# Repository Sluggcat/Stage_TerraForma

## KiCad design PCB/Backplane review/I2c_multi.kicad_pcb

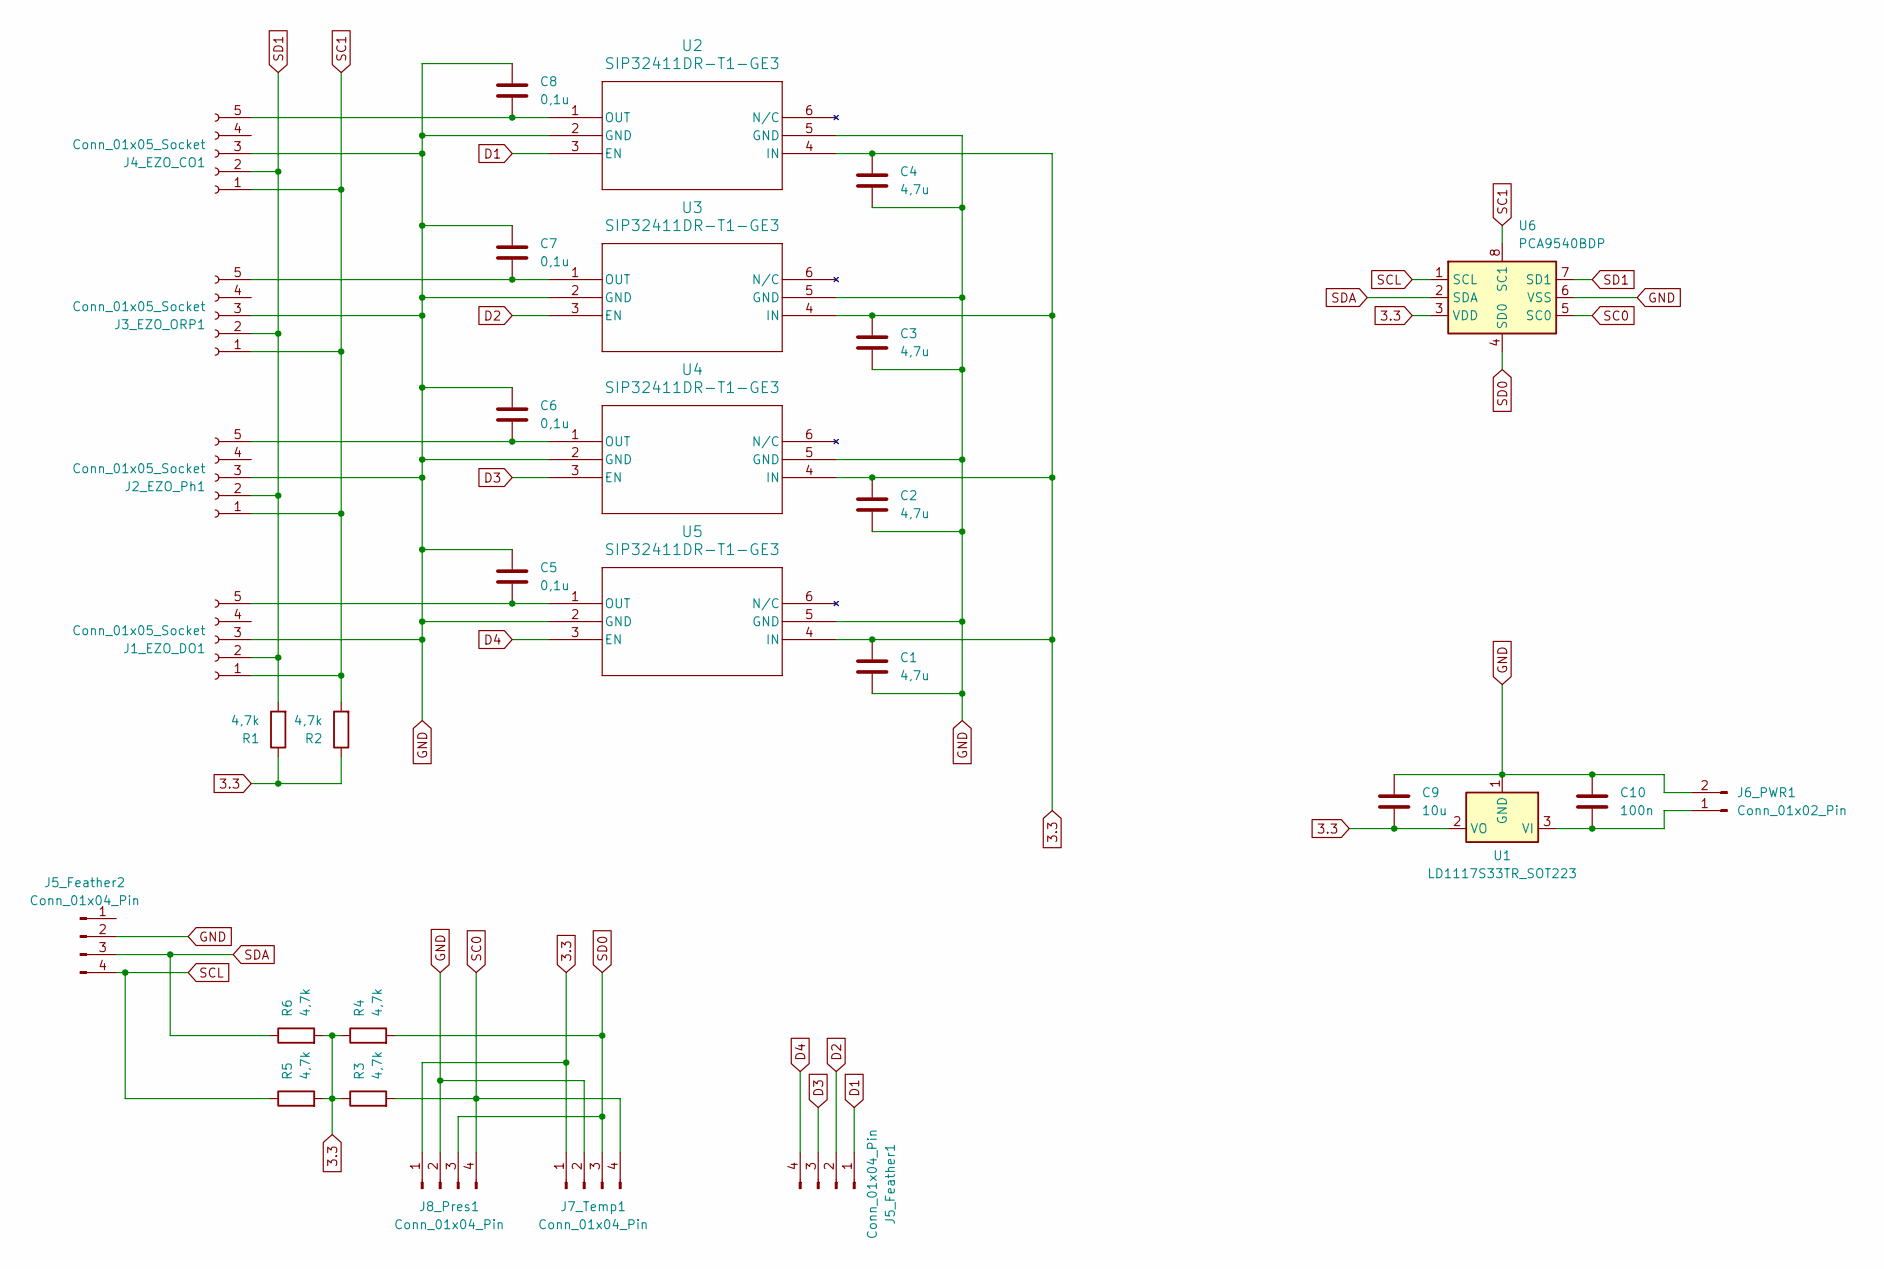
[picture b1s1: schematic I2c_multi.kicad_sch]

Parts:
C1, C2, C3, C4: 4,7u; C_0603_1608Metric_Pad1.08x0.95mm_HandSolder
C5, C6, C7, C8: 0,1u; C_0603_1608Metric_Pad1.08x0.95mm_HandSolder
C9: 10u; C_0603_1608Metric_Pad1.08x0.95mm_HandSolder
C10: 100n; C_0603_1608Metric_Pad1.08x0.95mm_HandSolder
J1_EZO_DO1, J2_EZO_Ph1, J3_EZO_ORP1, J4_EZO_CO1: Conn_01x05_Socket; PinSocket_1x05_P2.54mm_Vertical
J5_Feather1, J5_Feather2, J7_Temp1, J8_Pres1: Conn_01x04_Pin; PinSocket_1x04_P2.54mm_Vertical
J6_PWR1: Conn_01x02_Pin; PinSocket_1x02_P2.54mm_Vertical
R1, R2, R3, R4, R5, R6: 4,7k; R_0603_1608Metric_Pad0.98x0.95mm_HandSolder
U1: LD1117S33TR_SOT223; SOT-223-3_TabPin2
U2, U3, U4, U5: SIP32411DR-T1-GE3; SC_DR-T1-GE3_VIS
U6: PCA9540BDP; TSSOP-8_4.4x3mm_P0.65mm

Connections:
3.3: C1.2, C2.1, C3.1, C4.1, C9.2, J7_Temp1.1, J8_Pres1.1, R1.1, R2.1, R3.1, R4.1, R5.2, R6.2, U1.2 (VO), U2.4 (IN), U3.4 (IN), U4.4 (IN), U5.4 (IN), U6.3 (VDD)
D1: J5_Feather1.1, U2.3 (EN)
D2: J5_Feather1.2, U3.3 (EN)
D3: J5_Feather1.3, U4.3 (EN)
D4: J5_Feather1.4, U5.3 (EN)
GND: C1.1, C2.2, C3.2, C4.2, C5.1, C6.1, C7.1, C8.2, C9.1, C10.1, J1_EZO_DO1.3, J2_EZO_Ph1.3, J3_EZO_ORP1.3, J4_EZO_CO1.3, J5_Feather2.2, J6_PWR1.2, J7_Temp1.2, J8_Pres1.2, U1.1 (GND), U2.2 (GND), U2.5 (GND), U3.2 (GND), U3.5 (GND), U4.2 (GND), U4.5 (GND), U5.2 (GND), U5.5 (GND), U6.6 (VSS)
unnamed: C5.2, J1_EZO_DO1.5, U5.1 (OUT)
unnamed: C6.2, J2_EZO_Ph1.5, U4.1 (OUT)
unnamed: C7.2, J3_EZO_ORP1.5, U3.1 (OUT)
unnamed: C8.1, J4_EZO_CO1.5, U2.1 (OUT)
unnamed: C10.2, J6_PWR1.1, U1.3 (VI)
SC0: J7_Temp1.4, J8_Pres1.4, R3.2, U6.5 (SC0)
SC1: J1_EZO_DO1.1, J2_EZO_Ph1.1, J3_EZO_ORP1.1, J4_EZO_CO1.1, R2.2, U6.8 (SC1)
SCL: J5_Feather2.4, R5.1, U6.1 (SCL)
SD0: J7_Temp1.3, J8_Pres1.3, R4.2, U6.4 (SD0)
SD1: J1_EZO_DO1.2, J2_EZO_Ph1.2, J3_EZO_ORP1.2, J4_EZO_CO1.2, R1.2, U6.7 (SD1)
SDA: J5_Feather2.3, R6.1, U6.2 (SDA)

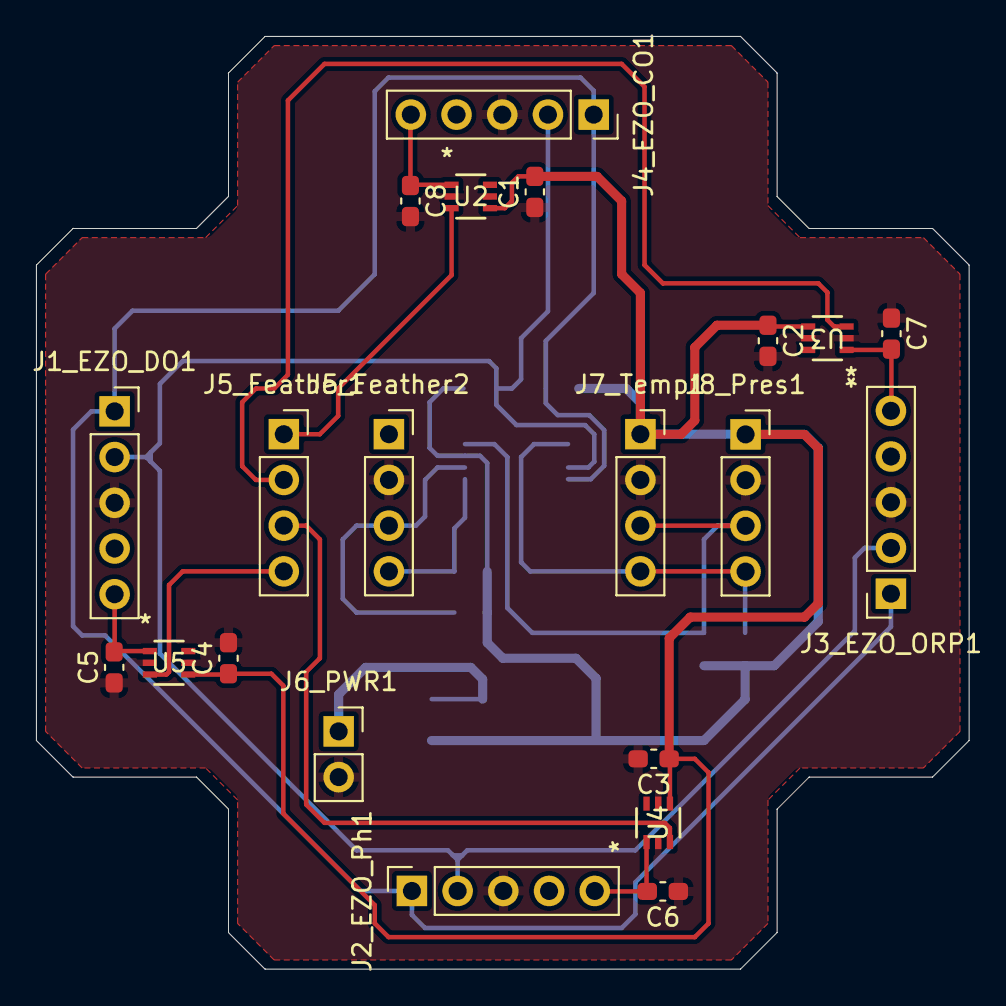
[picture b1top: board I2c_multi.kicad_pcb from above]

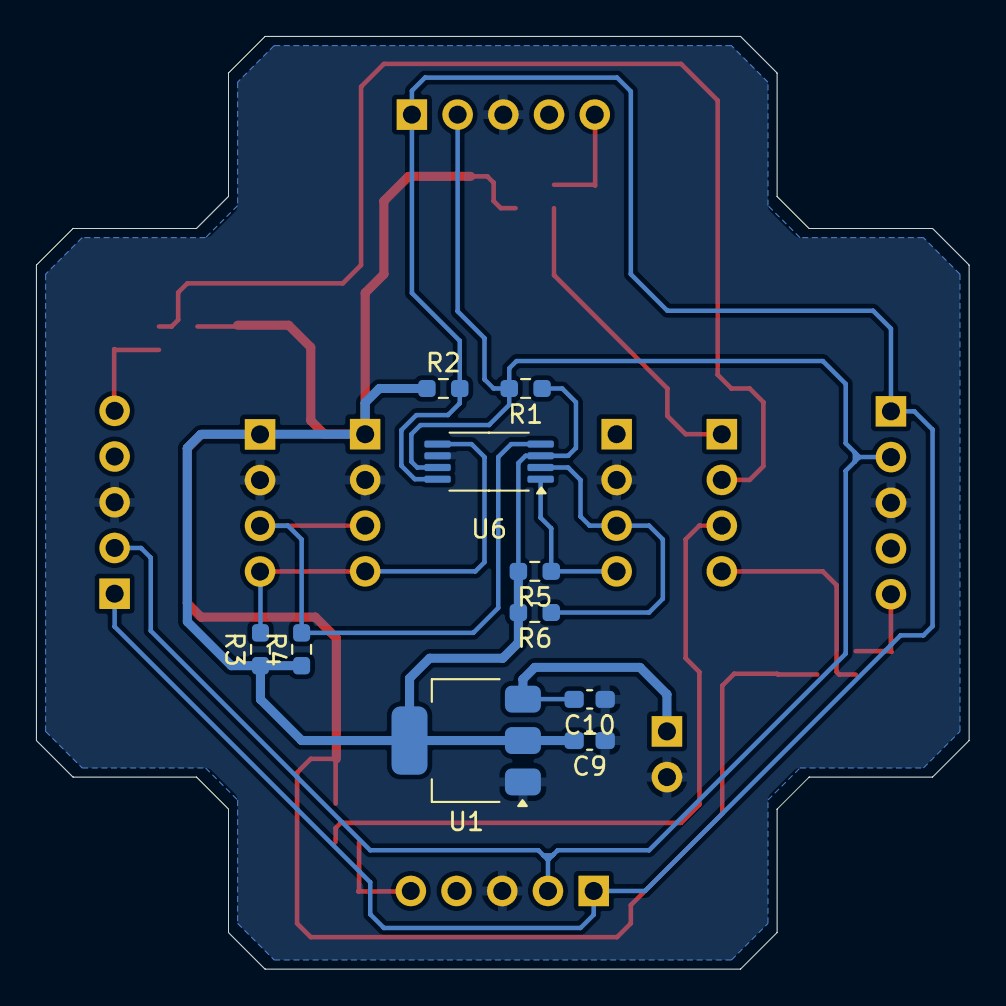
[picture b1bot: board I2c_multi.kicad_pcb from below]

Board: 2 copper layers, 51.8 x 51.8 mm, 31 parts (10 on the bottom side), 17 nets.

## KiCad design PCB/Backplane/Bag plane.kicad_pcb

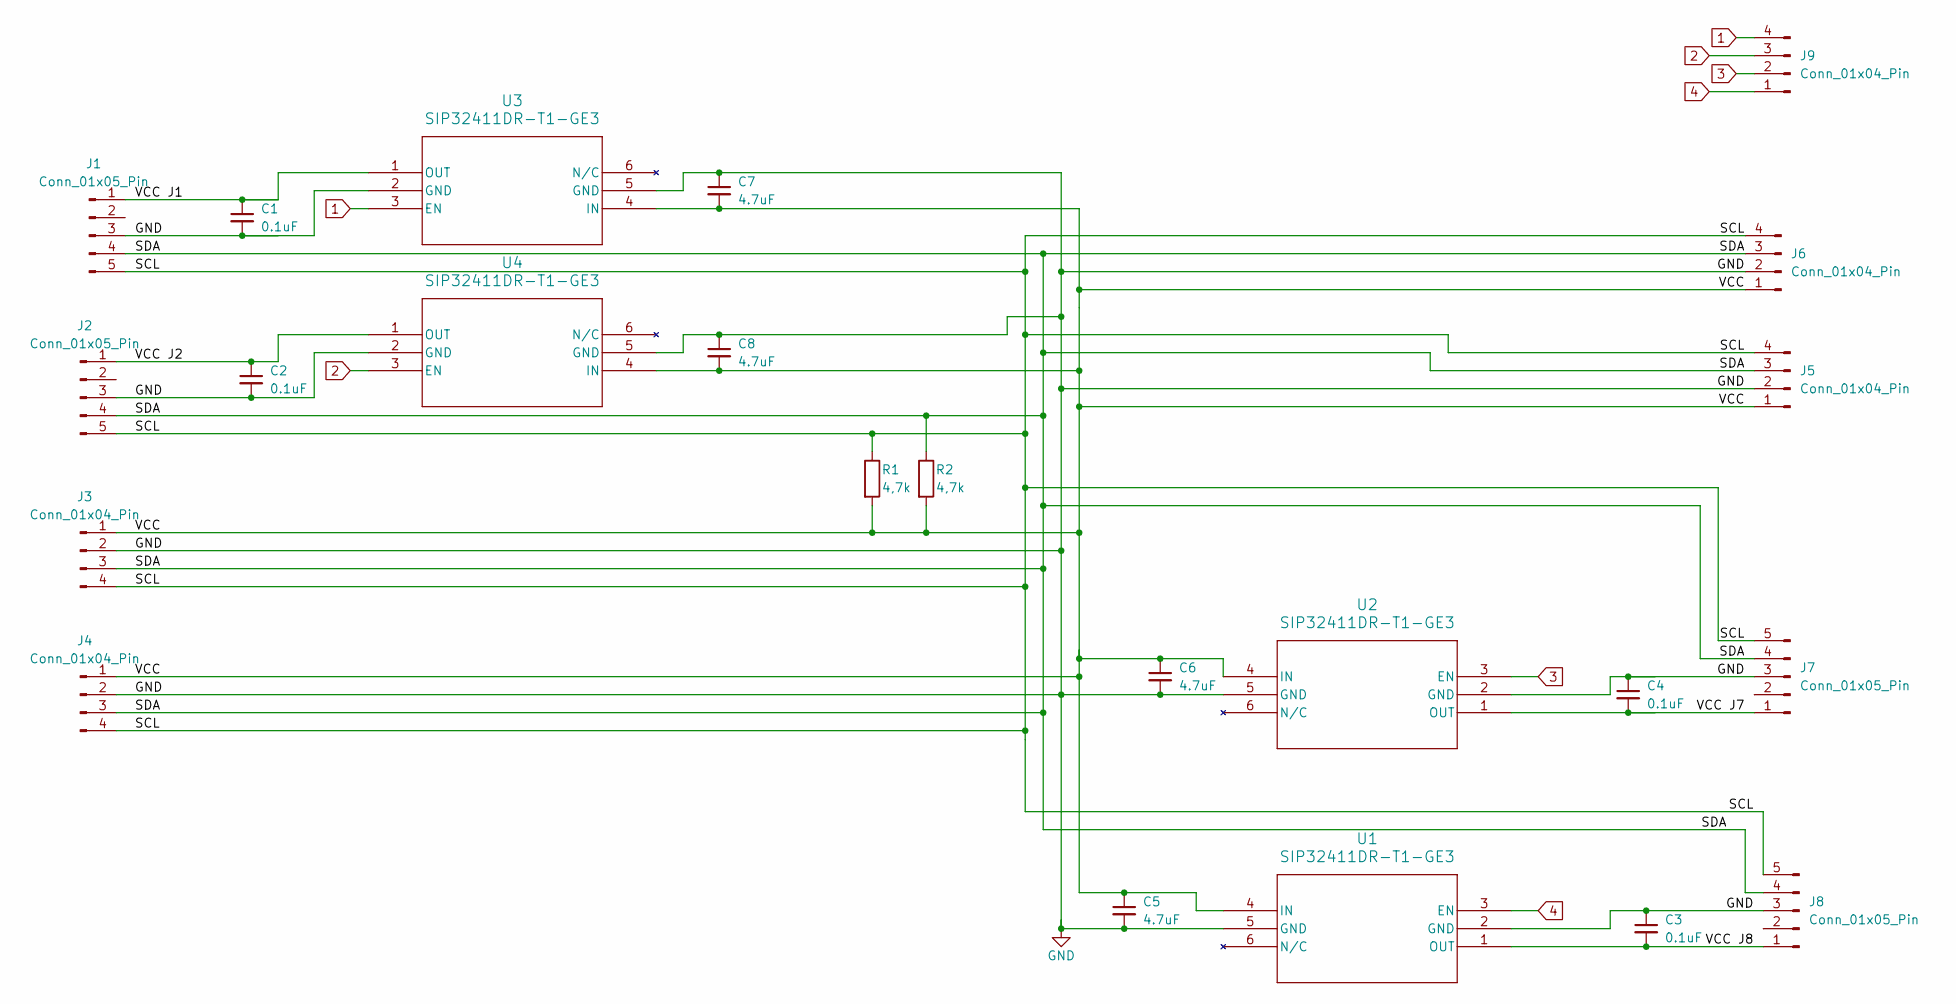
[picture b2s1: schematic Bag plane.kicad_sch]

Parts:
C1, C2, C3, C4: 0.1uF; C_0603_1608Metric
C5, C6, C7, C8: 4.7uF; C_0603_1608Metric
J1, J2, J7, J8: Conn_01x05_Pin; PinSocket_1x05_P2.54mm_Vertical
J3, J4, J5, J6, J9: Conn_01x04_Pin; PinHeader_1x04_P2.54mm_Vertical
R1, R2: 4,7k; R_0603_1608Metric
U1, U2, U3, U4: SIP32411DR-T1-GE3; SOT-363_SC-70-6

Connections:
1: J9.4, U3.3 (EN)
2: J9.3, U4.3 (EN)
3: J9.2, U2.3 (EN)
4: J9.1, U1.3 (EN)
/SCL: J1.5, J2.5, J3.4, J4.4, J5.4, J6.4, J7.5, J8.5, R1.1
/SDA: J1.4, J2.4, J3.3, J4.3, J5.3, J6.3, J7.4, J8.4, R2.1
/VCC: C5.1, C6.1, C7.2, C8.2, J3.1, J4.1, J5.1, J6.1, R1.2, R2.2, U1.4 (IN), U2.4 (IN), U3.4 (IN), U4.4 (IN)
/VCC J1: C1.1, J1.1, U3.1 (OUT)
/VCC J2: C2.1, J2.1, U4.1 (OUT)
/VCC J7: C4.2, J7.1, U2.1 (OUT)
/VCC J8: C3.2, J8.1, U1.1 (OUT)
GND: C1.2, C2.2, C3.1, C4.1, C5.2, C6.2, C7.1, C8.1, J1.3, J2.3, J3.2, J4.2, J5.2, J6.2, J7.3, J8.3, U1.2 (GND), U1.5 (GND), U2.2 (GND), U2.5 (GND), U3.2 (GND), U3.5 (GND), U4.2 (GND), U4.5 (GND)

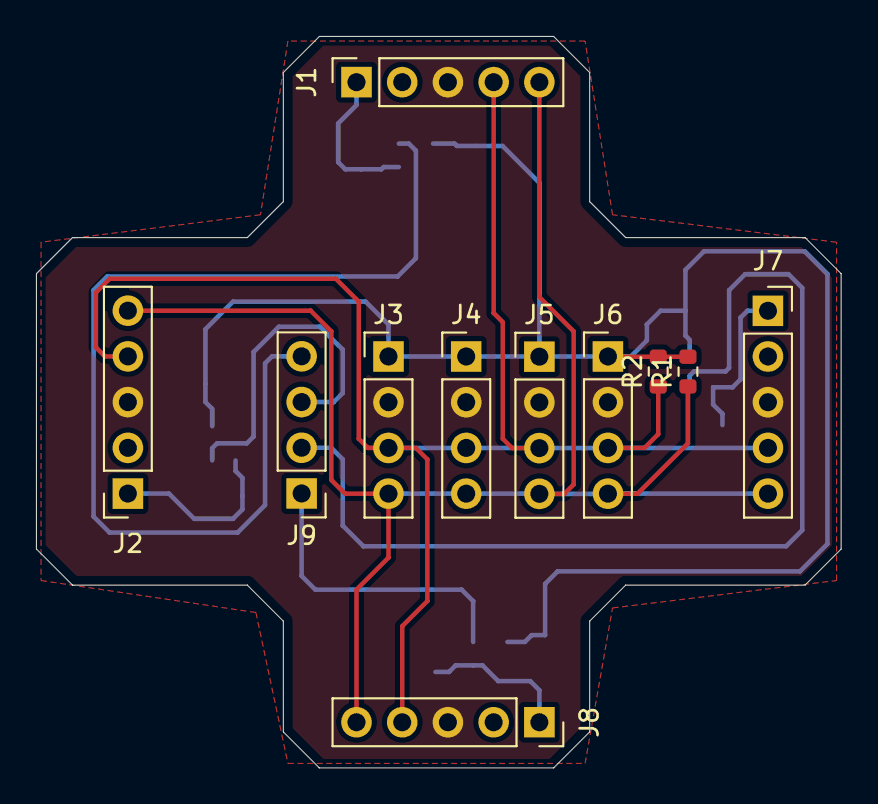
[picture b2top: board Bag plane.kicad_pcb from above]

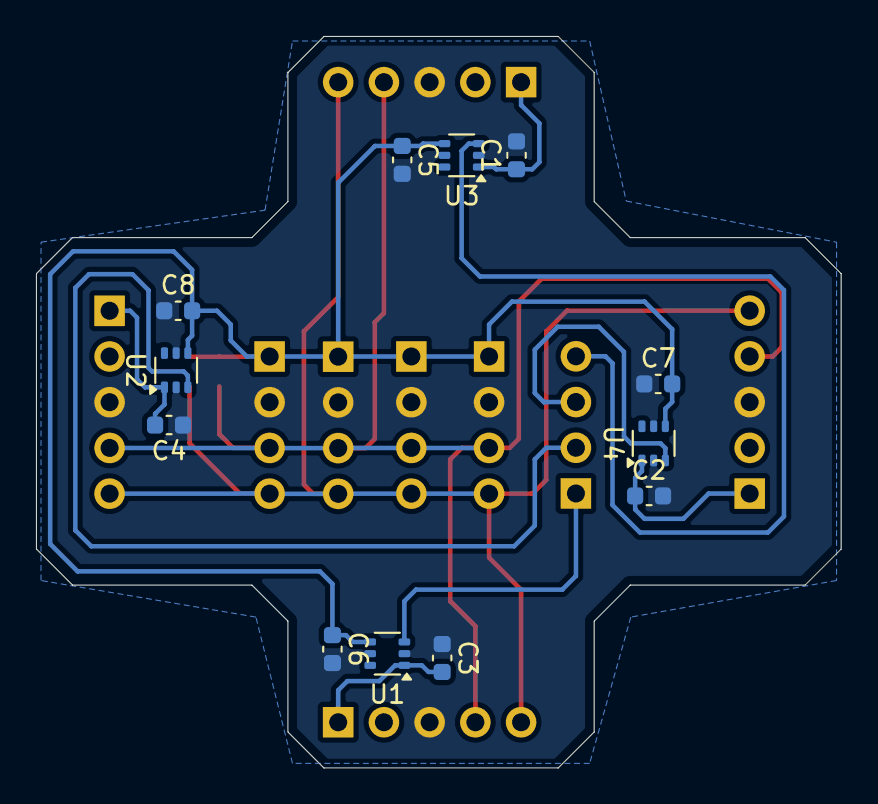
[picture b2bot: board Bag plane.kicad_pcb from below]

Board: 2 copper layers, 44.7 x 40.6 mm, 23 parts (12 on the bottom side), 12 nets.

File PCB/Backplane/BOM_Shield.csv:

Reference,Value,Datasheet,Footprint,Qty,Ref. Farnell,Ref. fabriquant
"C1,C2,C3,C4",0.1uF,~,Capacitor_SMD:C_0603_1608Metric,4,2904651,C0603C104K8RACAUTO
"C5,C6,C7,C8",4.7uF,~,Capacitor_SMD:C_0603_1608Metric,4,1572625,C0603C475K8PACTU
"J1,J2,J7,J8",Conn_01x05_Pin,~,Connector_PinSocket_2.54mm:PinSocket_1x05_P2.54mm_Vertical,4,2578707,SSW-105-01-G-S
"J3,J4,J5,J6,J9",Conn_01x04_Pin,~,Connector_PinHeader_2.54mm:PinHeader_1x04_P2.54mm_Vertical,5,,
"R1,R2","4,7k?",~,Resistor_SMD:R_0603_1608Metric,2,2073509,MCMR06X4701FTL
"U1,U2,U3,U4",SIP32411DR-T1-GE3,SIP32411DR-T1-GE3,Package_TO_SOT_SMD:SOT-363_SC-70-6,4,2361505,SIP32411DR-T1-GE3

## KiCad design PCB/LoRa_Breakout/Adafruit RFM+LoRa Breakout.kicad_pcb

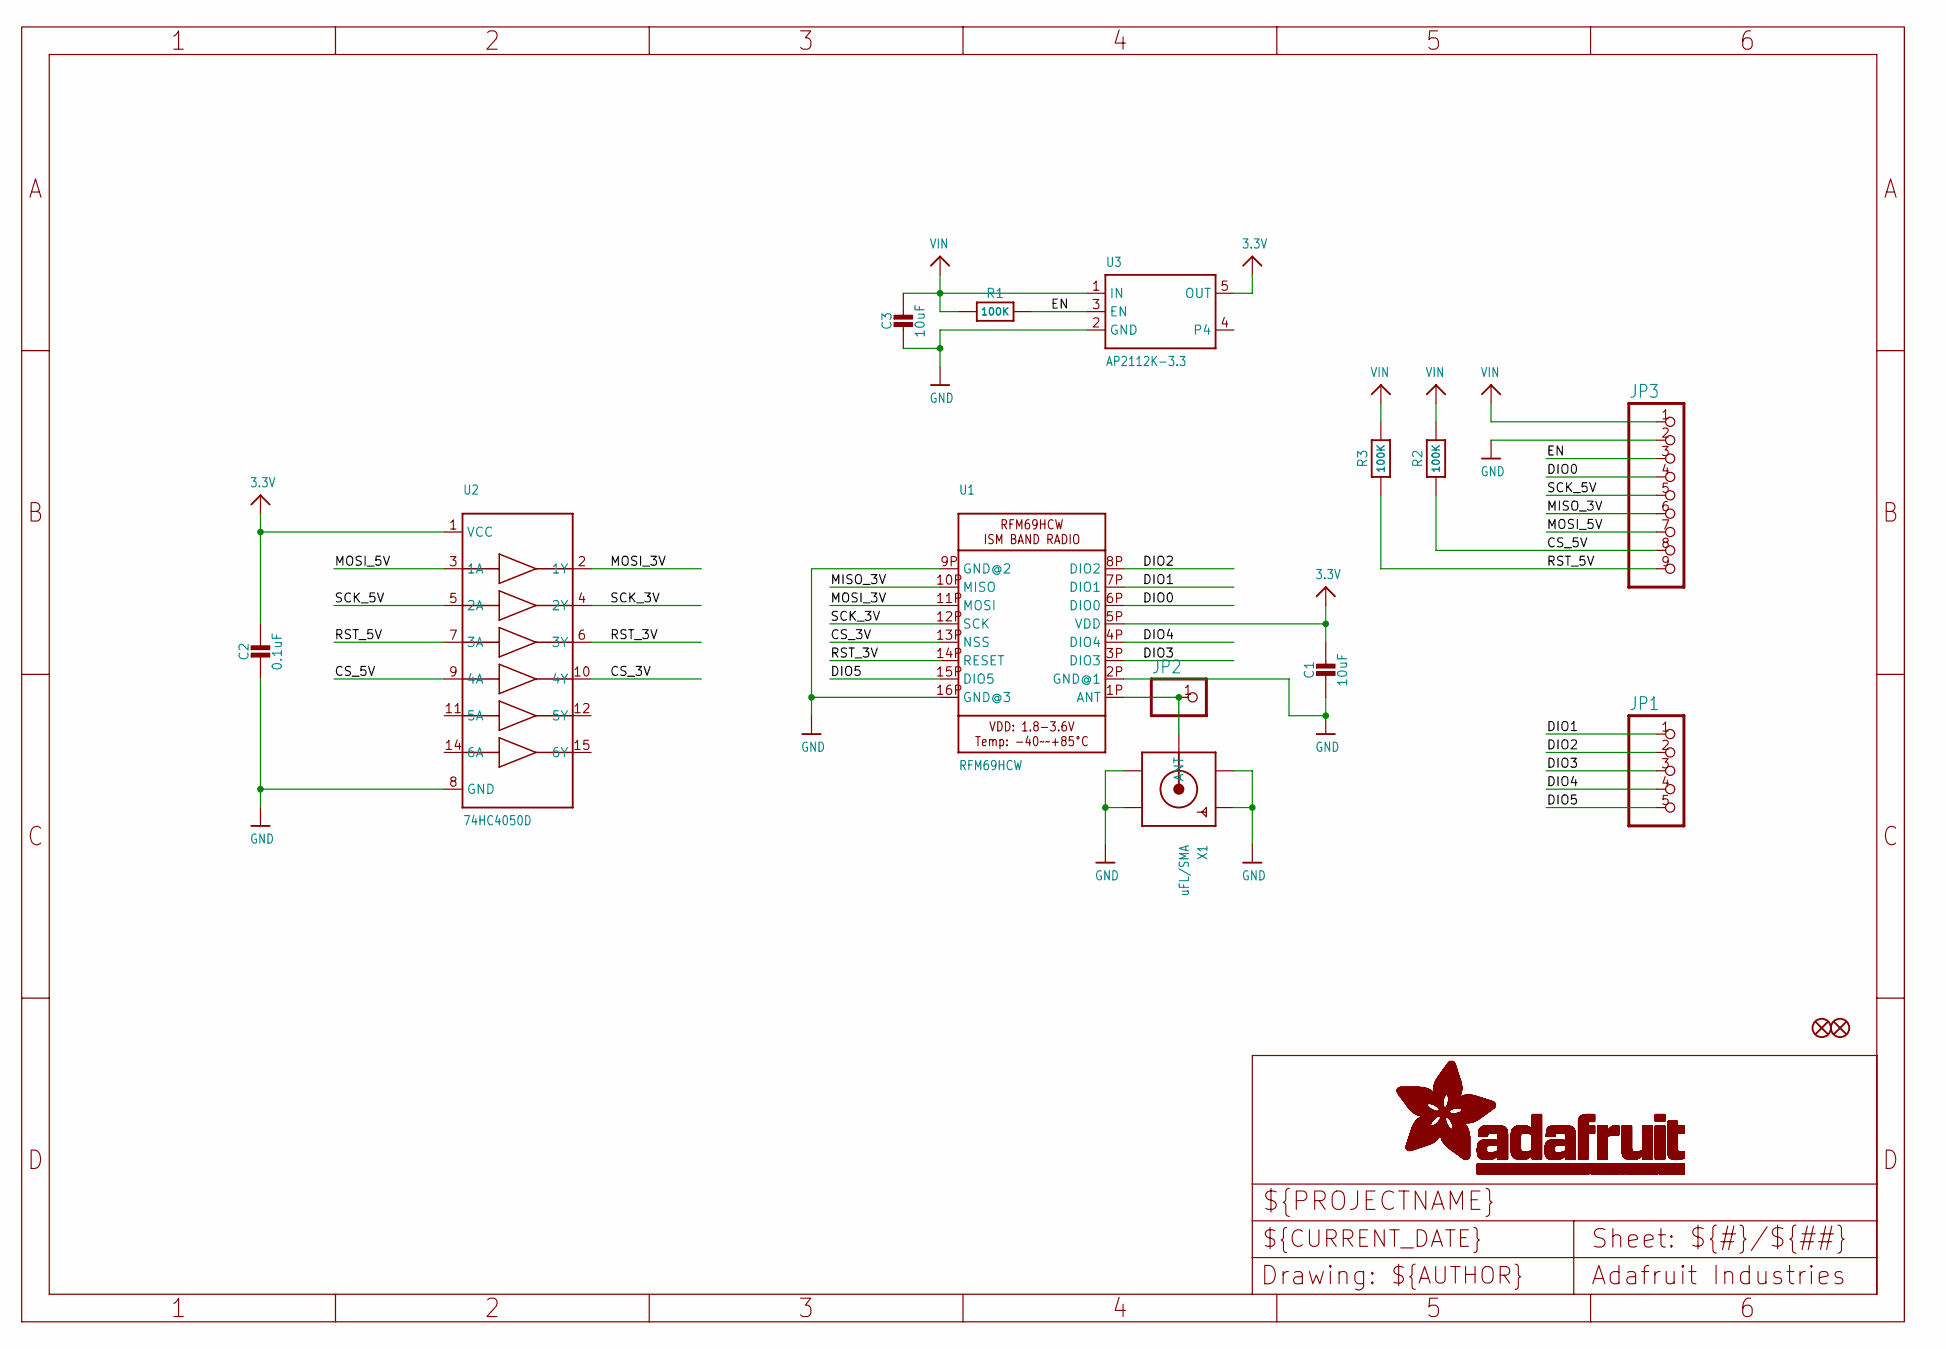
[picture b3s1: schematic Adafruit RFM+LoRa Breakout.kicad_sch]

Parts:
C1, C3: 10uF; 0805-NO
C2: 0.1uF; 0805-NO
FID1, FID2: FIDUCIAL""; FIDUCIAL_1MM
JP1: HEADER-1X570MIL; 1X05_ROUND_70
JP2: HEADER-1X1ROUND; 1X01_ROUND
JP3: HEADER-1X970MIL; 1X09_ROUND_70
R1, R2, R3: 100K; 0805-NO
U1: RFM69HCW; RFMHCW_SMT
U2: 74HC4050D; TSSOP16
U3: AP2112K-3.3; SOT23-5
X1: uFL/SMA; SMA_EDGELAUNCH_UFL

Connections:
3.3V: C1.1, C2.1, U1.5P (VDD), U2.1 (VCC), U3.5 (OUT)
CS_3V: U1.13P (NSS), U2.10 (4Y)
CS_5V: JP3.8, R2.1, U2.9 (4A)
DIO0: JP3.4, U1.6P (DIO0)
DIO1: JP1.1, U1.7P (DIO1)
DIO2: JP1.2, U1.8P (DIO2)
DIO3: JP1.3, U1.3P (DIO3)
DIO4: JP1.4, U1.4P (DIO4)
DIO5: JP1.5, U1.15P (DIO5)
EN: JP3.3, R1.2, U3.3 (EN)
GND: C1.2, C2.2, C3.2, JP3.2, U1.2P (GND@1), U1.9P (GND@2), U1.16P (GND@3), U2.8 (GND), U3.2 (GND), X1.GND@1 (GND1), X1.GND@2 (GND2), X1.GND@3 (GND3), X1.GND@4 (GND4)
MISO_3V: JP3.6, U1.10P (MISO)
MOSI_3V: U1.11P (MOSI), U2.2 (1Y)
MOSI_5V: JP3.7, U2.3 (1A)
unnamed: JP2.1, U1.1P (ANT), X1.P (ANT)
RST_3V: U1.14P (RESET), U2.6 (3Y)
RST_5V: JP3.9, R3.1, U2.7 (3A)
SCK_3V: U1.12P (SCK), U2.4 (2Y)
SCK_5V: JP3.5, U2.5 (2A)
VIN: C3.1, JP3.1, R1.1, R2.2, R3.2, U3.1 (IN)

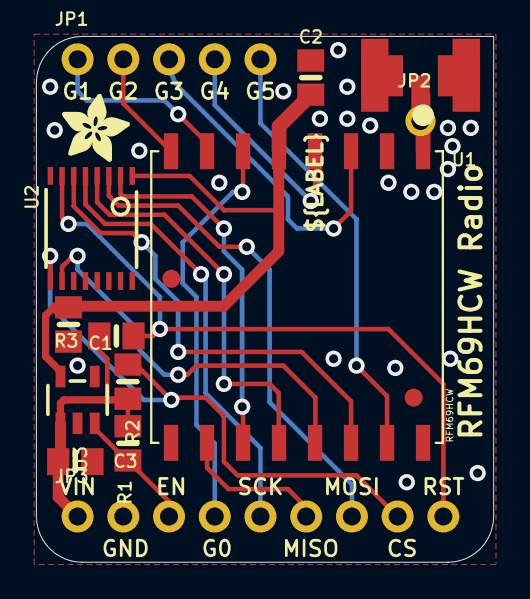
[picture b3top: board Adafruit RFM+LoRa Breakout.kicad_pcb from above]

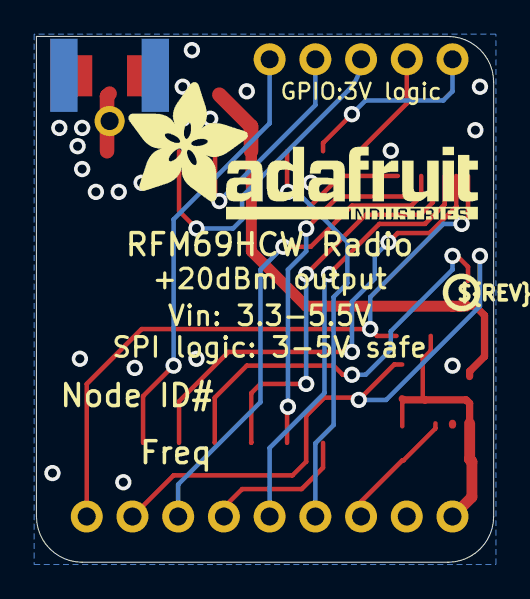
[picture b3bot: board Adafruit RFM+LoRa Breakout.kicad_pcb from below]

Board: 2 copper layers, 25.4 x 29.2 mm, 18 parts (2 on the bottom side), 20 nets.

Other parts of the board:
U$8: ADAFRUIT_3.5MM
U$14: PCBFEAT-REV-040
U$19: ADAFRUIT_TEXT_20MM

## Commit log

2024-06-04 Create .gitignore
    Only import useful files
2024-06-05 First Upload
    Vanilla files for old systems
2024-06-06 minor arrangements
    spacings in code
    folder names
2024-06-10 Backplane PCB
    upload Kicad project files
2024-06-10 Reorganizing
2024-06-10 Create Comms.py
    Communications manager :
    TTN class
2024-06-10 create main
2024-06-10 create setup
2024-06-11 Upload RFM9X lib
    µPython variant adapted from adafruit CircuitPython
2024-06-11 add License
2024-06-11 reorganizing files
2024-06-12 Add reference code
    from https://github.com/lemariva/uPyLoRaWAN/tree/LoRaWAN
2024-06-12 edit config.py
2024-06-13 Updated µBus adapter
    power redirected to 3.3V
2024-06-14 Commit Kristen
2024-06-17 Reroganizing files
    yet again
2024-06-17 Test ok
    read temp and version_reg.
    bytearray sent to server (fixed by resync)
2024-06-20 Modification programme Boopy
2024-06-20 Update
    separated initilizations from main programm into a config.py script
2024-06-20 Renamed folder
2024-06-20 Updated Kicad project
2024-06-21 Ajout bibliothèque programme Arduino
2024-06-24 Modification librairie 24/06
2024-06-24 Mise à jour des librairies A debug
2024-06-24 Corrections : -Ajout de la fonction calc_salinity dans le header atlas
2024-06-25 Upload Terra Forma code
    tried to reorganize
    need to debug
2024-06-26 Code refactoring
    Hide settings
    Separated sensors fuctions from main program
2024-06-26 cleanup
2024-06-26 remove non working code
2024-06-26 yet another cleanup
    Made a library for file editing stuff
2024-06-27 minor cleanup
2024-06-27 Update TerraForma_3inch.ino
    check if file is created in SD card (failed)
2024-07-03 Datalogger fix attempt
    SD initialized
    Crash when trying to create files
2024-07-04 Debugging Datalogger
    SD is fine can write and read files
    RTC initialized correctly
    calling rtc.now() freeze the program with sensors, yet works standalone
2024-07-05 Commit connexion UART Boopy to Feather
2024-07-05 Code Arduino UART
2024-07-08 add functionality
    send data over Serial
2024-07-08 Decodage du port serie
2024-07-08 Reorganizing files
    added : 3 scripts to receive data from the probe
2024-07-09 Upload Boopy code
    Receive data over serial and send them by LoRa. All done in aasynchronous mode.
    Need to find a way to store Frame Counter
2024-07-10 Update Terra Forma
    changed acquisition cycle to use load switches
2024-07-11 Ajout fonction GPS/RTC et SD pour Boopy (debuggage)
2024-07-11 Modification pour ajouter le debuggage SD manquant
2024-07-12 Add GPS and SD card controller Missing RTC allarm
2024-07-12 small cleanup
2024-07-15 Fixing update
    - solved hardware issue : no more freeze when all Ezo sensors disabled
    - I2C multiplexer added
    - small fixes on the LoRa transmitter
2024-07-15 Modify RTC for boopy and test Everything seems to be working properly
2024-07-16 Bug fixes
    Added voltage regulator for Atlas.
    Temp. and Pressure. sensors bugged due to OLED display. Fixed in initialization sequence, display goes first now.
2024-07-16 Add folder Archive for debug Alarm RTC works and the system restart automatically
2024-07-16 Add condition on RTC lib If parameter is 0x00 register value will be 0x80 Register remain unused with 0x80
2024-07-16 Still fixing OLED
2024-07-22 Update
    minor changes before power tests
2024-07-22 minor cleanups
2024-07-22 Program testing conversion of data : integer to bytearray to sending on LoRa Compiling done conversion working well
2024-07-22 Add Decode bytearray to binary command
2024-07-23 Modifying conversion byte array functions to simplify them Seems working well and adding decode bytes to send messages and parameters to sensors Debug program with comments
2024-07-23 Correction in the function int_to_byte, wrong parameter
2024-07-23 Cleanup update
    removed non used variables
    added some descriptions for doc.
    minor code refactoring here and there
2024-07-23 Oled bug fixes
    ATLAS ON for a correct initialization
2024-07-23 Update TerraForma.ino
    delete useless stuff
2024-07-24 Update TerraForma.ino
    cleanup
2024-07-26 Adding and testing UART communication Adding sign bits to check if datas are positive or negative Data are stored on SD card on Boopy LoRa communication is under comment to prevent lot of transmissio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
2024-07-31 Adding frame counter for LoRa communication Correction of payload to a signe bit for only one value, not integer and decimal value Adding new PCB files in Backplane review : - Add voltage regulator -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
2024-08-27 Reversing changes
    for testing purposes
2024-08-27 Add sleep mode
    the probe goes to sleep after 5 measurements.
    wire pin 9 to GND to wake up
